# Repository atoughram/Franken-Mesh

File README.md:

# Franken-Mesh
## DIY 1W LORA Node for Meshtastic

A Meshtastic project using a 30dbm (1W) LORA Radio (E22-900M30S) and an EPS32-DEVKIT-V1.  The circuit also adds four I2C ports for other sensors like a BME280 enviromental sensor, or any other sensor suported by Meshtastic.  There is also a TTL serial port for use with a GPS module and a ssd1306 connector if a Oled screen is wanted.

I've used this for both mobile and fixed operations with good luck.  There are STL files for a 3d printing a simple enclosure for the PCB.

![Franken-Mesh] (images/PXL_20240928_021302629.jpg) 

MIT License

Copyright (c) 2025 atoughram

Permission is hereby granted, free of charge, to any person obtaining a copy
of this software and associated documentation files (the "Software"), to deal
in the Software without restriction, including without limitation the rights
to use, copy, modify, merge, publish, distribute, sublicense, and/or sell
copies of the Software, and to permit persons to whom the Software is
furnished to do so, subject to the following conditions:

The above copyright notice and this permission notice shall be included in all
copies or substantial portions of the Software.

THE SOFTWARE IS PROVIDED "AS IS", WITHOUT WARRANTY OF ANY KIND, EXPRESS OR
IMPLIED, INCLUDING BUT NOT LIMITED TO THE WARRANTIES OF MERCHANTABILITY,
FITNESS FOR A PARTICULAR PURPOSE AND NONINFRINGEMENT. IN NO EVENT SHALL THE
AUTHORS OR COPYRIGHT HOLDERS BE LIABLE FOR ANY CLAIM, DAMAGES OR OTHER
LIABILITY, WHETHER IN AN ACTION OF CONTRACT, TORT OR OTHERWISE, ARISING FROM,
OUT OF OR IN CONNECTION WITH THE SOFTWARE OR THE USE OR OTHER DEALINGS IN THE
SOFTWARE.

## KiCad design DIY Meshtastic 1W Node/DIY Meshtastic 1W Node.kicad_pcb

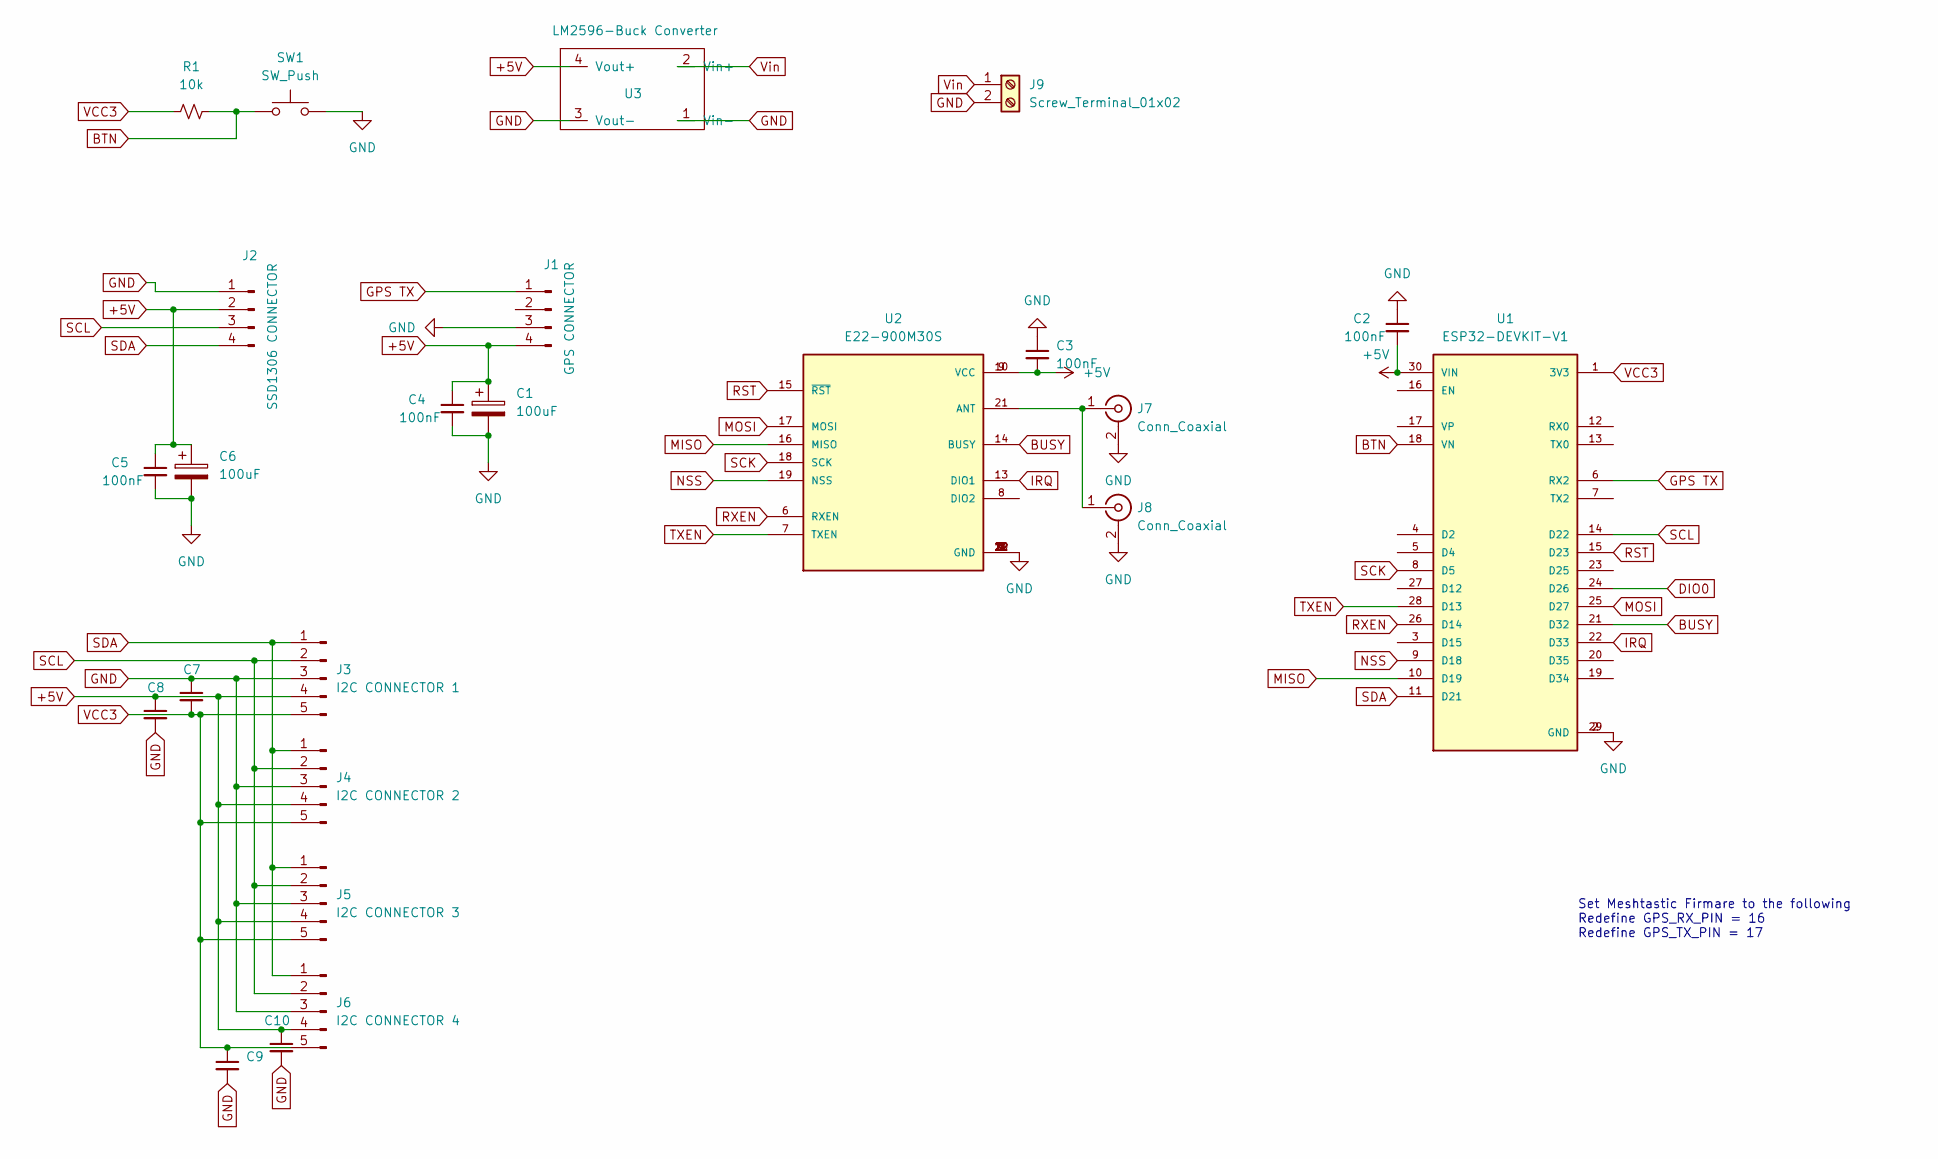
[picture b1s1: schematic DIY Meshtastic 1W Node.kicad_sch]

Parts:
C1, C6: 100uF; CP_Elec_6.3x7.7
C2, C3, C4, C5: 100nF; R_1206_3216Metric_Pad1.30x1.75mm_HandSolder
C7, C8, C9, C10: 100nf; R_1206_3216Metric_Pad1.30x1.75mm_HandSolder
J1: GPS CONNECTOR; PinHeader_1x04_P2.54mm_Vertical
J2: SSD1306 CONNECTOR; PinHeader_1x04_P2.54mm_Vertical
J3: I2C CONNECTOR 1; PinHeader_1x05_P2.54mm_Vertical
J4: I2C CONNECTOR 2; PinHeader_1x05_P2.54mm_Vertical
J5: I2C CONNECTOR 3; PinHeader_1x05_P2.54mm_Vertical
J6: I2C CONNECTOR 4; PinHeader_1x05_P2.54mm_Vertical
J7: Conn_Coaxial; SMA_Amphenol_901-144_Vertical
J8: Conn_Coaxial; SMA_Samtec_SMA-J-P-X-ST-EM1_EdgeMount
J9: Screw_Terminal_01x02; TerminalBlock_bornier-2_P5.08mm
R1: 10k; R_1206_3216Metric_Pad1.30x1.75mm_HandSolder
SW1: SW_Push; SW_PUSH_6mm
U1: ESP32-DEVKIT-V1; MODULE_ESP32_DEVKIT_V1; PARTREV N/A
U2: E22-900M30S; XCVR_E22-900M30S; PARTREV 1.2
U3: LM2596-Buck Converter; LM2596_HW_411

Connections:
+5V: C1.1, C2.2, C3.2, C4.1, C5.1, C6.1, C8.1, C10.1, J1.4, J2.2, J3.4, J4.4, J5.4, J6.4, U1.30 (VIN), U2.9 (VCC), U2.10 (VCC), U3.4 (Vout+)
BTN: R1.1, SW1.1, U1.18 (VN)
BUSY: U1.21 (D32), U2.14 (BUSY)
DIO0: U1.24 (D26)
GND: C1.2, C2.1, C3.1, C4.2, C5.2, C6.2, C7.1, C8.2, C9.2, C10.2, J1.3, J2.1, J3.3, J4.3, J5.3, J6.3, J7.2 (Ext), J8.2 (Ext), J9.2, SW1.2, U1.2 (GND), U1.29 (GND), U2.1 (GND), U2.2 (GND), U2.3 (GND), U2.4 (GND), U2.5 (GND), U2.11 (GND), U2.12 (GND), U2.20 (GND), U2.22 (GND), U3.1 (Vin-), U3.3 (Vout-)
GPS TX: J1.1, U1.6 (RX2)
IRQ: U1.22 (D33), U2.13 (DIO1)
MISO: U1.10 (D19), U2.16 (MISO)
MOSI: U1.25 (D27), U2.17 (MOSI)
NSS: U1.9 (D18), U2.19 (NSS)
unnamed: J7.1 (In), J8.1 (In), U2.21 (ANT)
RST: U1.15 (D23), U2.15 (~RST)
RXEN: U1.26 (D14), U2.6 (RXEN)
SCK: U1.8 (D5), U2.18 (SCK)
SCL: J2.3, J3.2, J4.2, J5.2, J6.2, U1.14 (D22)
SDA: J2.4, J3.1, J4.1, J5.1, J6.1, U1.11 (D21)
TXEN: U1.28 (D13), U2.7 (TXEN)
VCC3: C7.2, C9.1, J3.5, J4.5, J5.5, J6.5, R1.2, U1.1 (3V3)
Vin: J9.1, U3.2 (Vin+)

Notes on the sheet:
Set Meshtastic Firmare to the following Redefine GPS_RX_PIN = 16 Redefine GPS_TX_PIN = 17

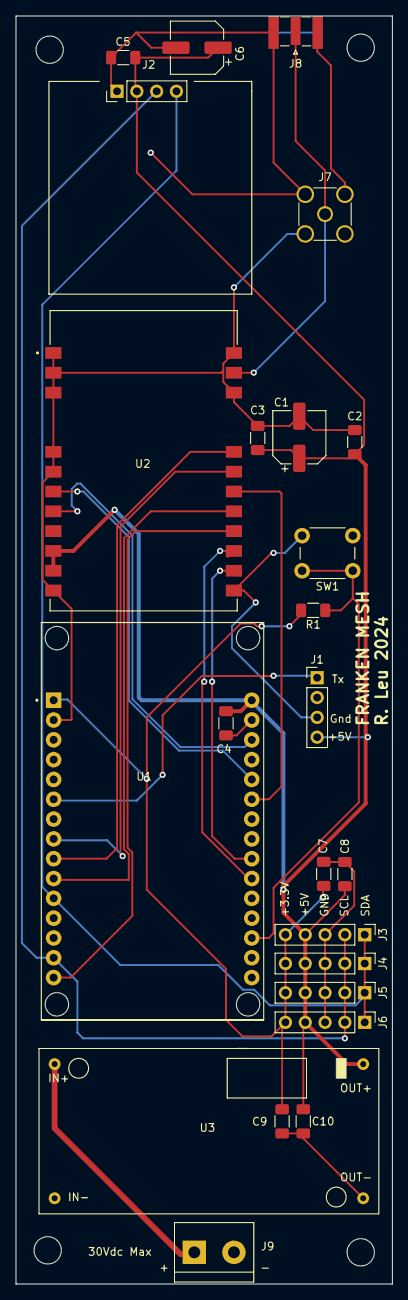
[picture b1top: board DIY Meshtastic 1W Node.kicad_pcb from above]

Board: 2 copper layers, 48.3 x 162.6 mm, 24 parts (0 on the bottom side), 18 nets.

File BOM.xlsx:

Description | Value | Reference | Qty | Footprint | Price | URL
Capacitor | 100nf | C2, C3, C4, C5, C7, C8, C9, C10 | 8 | Resistor_SMD:R_1206_3216Metric_Pad1.30x1.75mm_HandSolder | 1.26 | https://www.aliexpress.us/item/3256805505305288.html?spm=a2g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
Capacitor | 100uf | C1, C6 | 2 | Capacitor_SMD:CP_Elec_6.3x7.7 | 1.62 | https://www.aliexpress.us/item/3256804775943180.html?spm=a2g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
Resistor | 10K | R1 | 1 | Resistor_SMD:R_1206_3216Metric_Pad1.30x1.75mm_HandSolder | 1.07 | https://www.aliexpress.us/item/3256805494865143.html?spm=a2g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
Microcontroller | ESP32-DEVKIT-V1 | U1 | 1 |  | 3.79 | https://www.aliexpress.us/item/3256802944254383.html?spm=a2g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
30dbm LORA Radio | E22-900M30S | U2 | 1 |  | 7.39 | https://www.aliexpress.us/item/2255800357606493.html?spm=a2g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
SMA Connector |  | J7, J8 | 1 | Connector_Coaxial:SMA_Amphenol_901-144_Vertical | 2.31 | https://www.aliexpress.us/item/3256802990049867.html?spm=a2g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
Switch |  | SW1 | 1 | Button_Switch_THT:SW_PUSH_6mm | 0.25 | https://www.aliexpress.us/item/3256802876527512.html?spm=a2g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
Display | SSD1306 |  | 1 |  | 1.65 | https://www.aliexpress.us/item/3256807290188213.html?spm=a2g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
Buck Converter | LM2596 | U3 | 1 |  | 1.23 | https://www.aliexpress.us/item/3256806546818317.html?spm=a2g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
Screw Terminal |  | J9 | 1 | TerminalBlock:TerminalBlock_bornier-2_P5.08mm | 1.32 | https://www.aliexpress.us/item/3256806456550715.html?spm=a2g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
Male 5 pin Header |  | J3 - J6 | 4 | Connector_PinHeader_2.54mm:PinHeader_1x05_P2.54mm_Vertical | 1.91 | https://www.aliexpress.us/item/2255800687544049.html?spm=a2g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
Female 15 pin Header |  |  | 2 |  | 1.91 | https://www.aliexpress.us/item/2255800687544049.html?spm=a2g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

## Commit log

2024-09-28 Initial Commit
    Initial Commit
2024-09-28 Minor Change to the schematic
    Add values for a couple of capacitors I forgot.
2024-10-07 Added STL Files
2024-10-08 Modified the Schematic, and PCB
    Added some documentation on the schematic and PCB, regenerated gerbers
2024-10-13 Incremental commit
    Fixed some of the front silkscreen and added an STL File
2024-10-13 Updated Gerbers
2024-10-18 Incremental Commit
2025-01-18 Modified the Readme.md file
2025-01-18 Modified readme.md
2025-02-03 Updated Commit
2025-10-17 Added the Schematic
    in Images directory
